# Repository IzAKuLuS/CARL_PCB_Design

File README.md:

This branch contains the PCB project for the battery management system project.

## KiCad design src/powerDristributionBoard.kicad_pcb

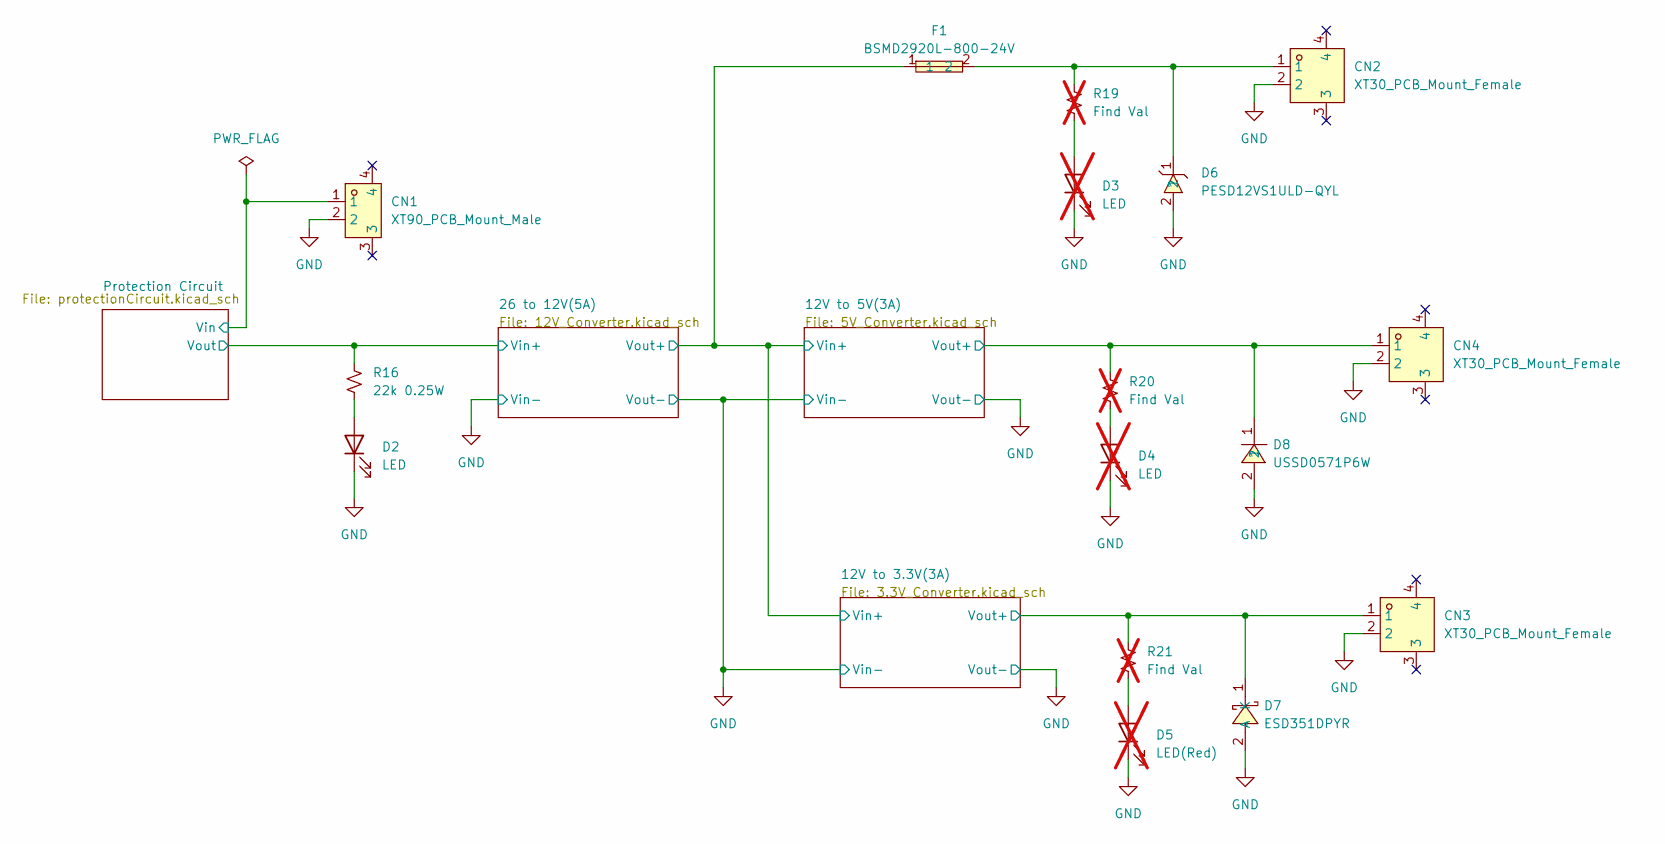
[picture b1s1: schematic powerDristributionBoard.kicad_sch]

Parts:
CN1: XT90_PCB_Mount_Male; XT-90_PCB_Mount_Male; MPN XT90PW-M.G.Y; LCSC Part C3040689
CN2, CN3, CN4: XT30_PCB_Mount_Female; MPN XT30PW-F20.G.Y; LCSC Part C2913282
D2: LED; LED_1206_3216Metric; MPN E7YYD; LCSC Part C55382848
D3, D4: LED; LED_0603_1608Metric; not fitted
D5: LED(Red); LED_0603_1608Metric; not fitted
D6: PESD12VS1ULD-QYL; MPN PESD12VS1ULD-QYL; LCSC Part C7508737
D7: ESD351DPYR; MPN ESD351DPYR; LCSC Part C1974929
D8: USSD0571P6W; MPN USSD0571P6W; LCSC Part C5272748
F1: BSMD2920L-800-24V; MPN BSMD2920L-800-24V; LCSC Part C51025748
R16: 22k 0.25W; R_1206_3216Metric; MPN HRC1206J223 HNTN; LCSC Part C54921593
R19, R20, R21: Find Val; R_0603_1608Metric; not fitted

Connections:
/12V to 3.3V(3A)/Vout+: CN3.1, D7.1 (K), R21.1; also elsewhere on the board
/12V to 5V(3A)/Vout+: CN4.1, D8.1, R20.1; also elsewhere on the board
/26 to 12V(5A)/Rsense+: F1.1; also elsewhere on the board
/Protection Circuit/Vin: CN1.1; also elsewhere on the board
GND: CN1.2, CN2.2, CN3.2, CN4.2, D2.1 (K), D3.1 (K), D4.1 (K), D5.1 (K), D6.2, D7.2 (A), D8.2; also elsewhere on the board
LM_Vin: R16.1; also elsewhere on the board
unnamed: CN2.1, D6.1, F1.2, R19.1
unnamed: D2.2 (A), R16.2
unnamed: D3.2 (A), R19.2
unnamed: D4.2 (A), R20.2
unnamed: D5.2 (A), R21.2

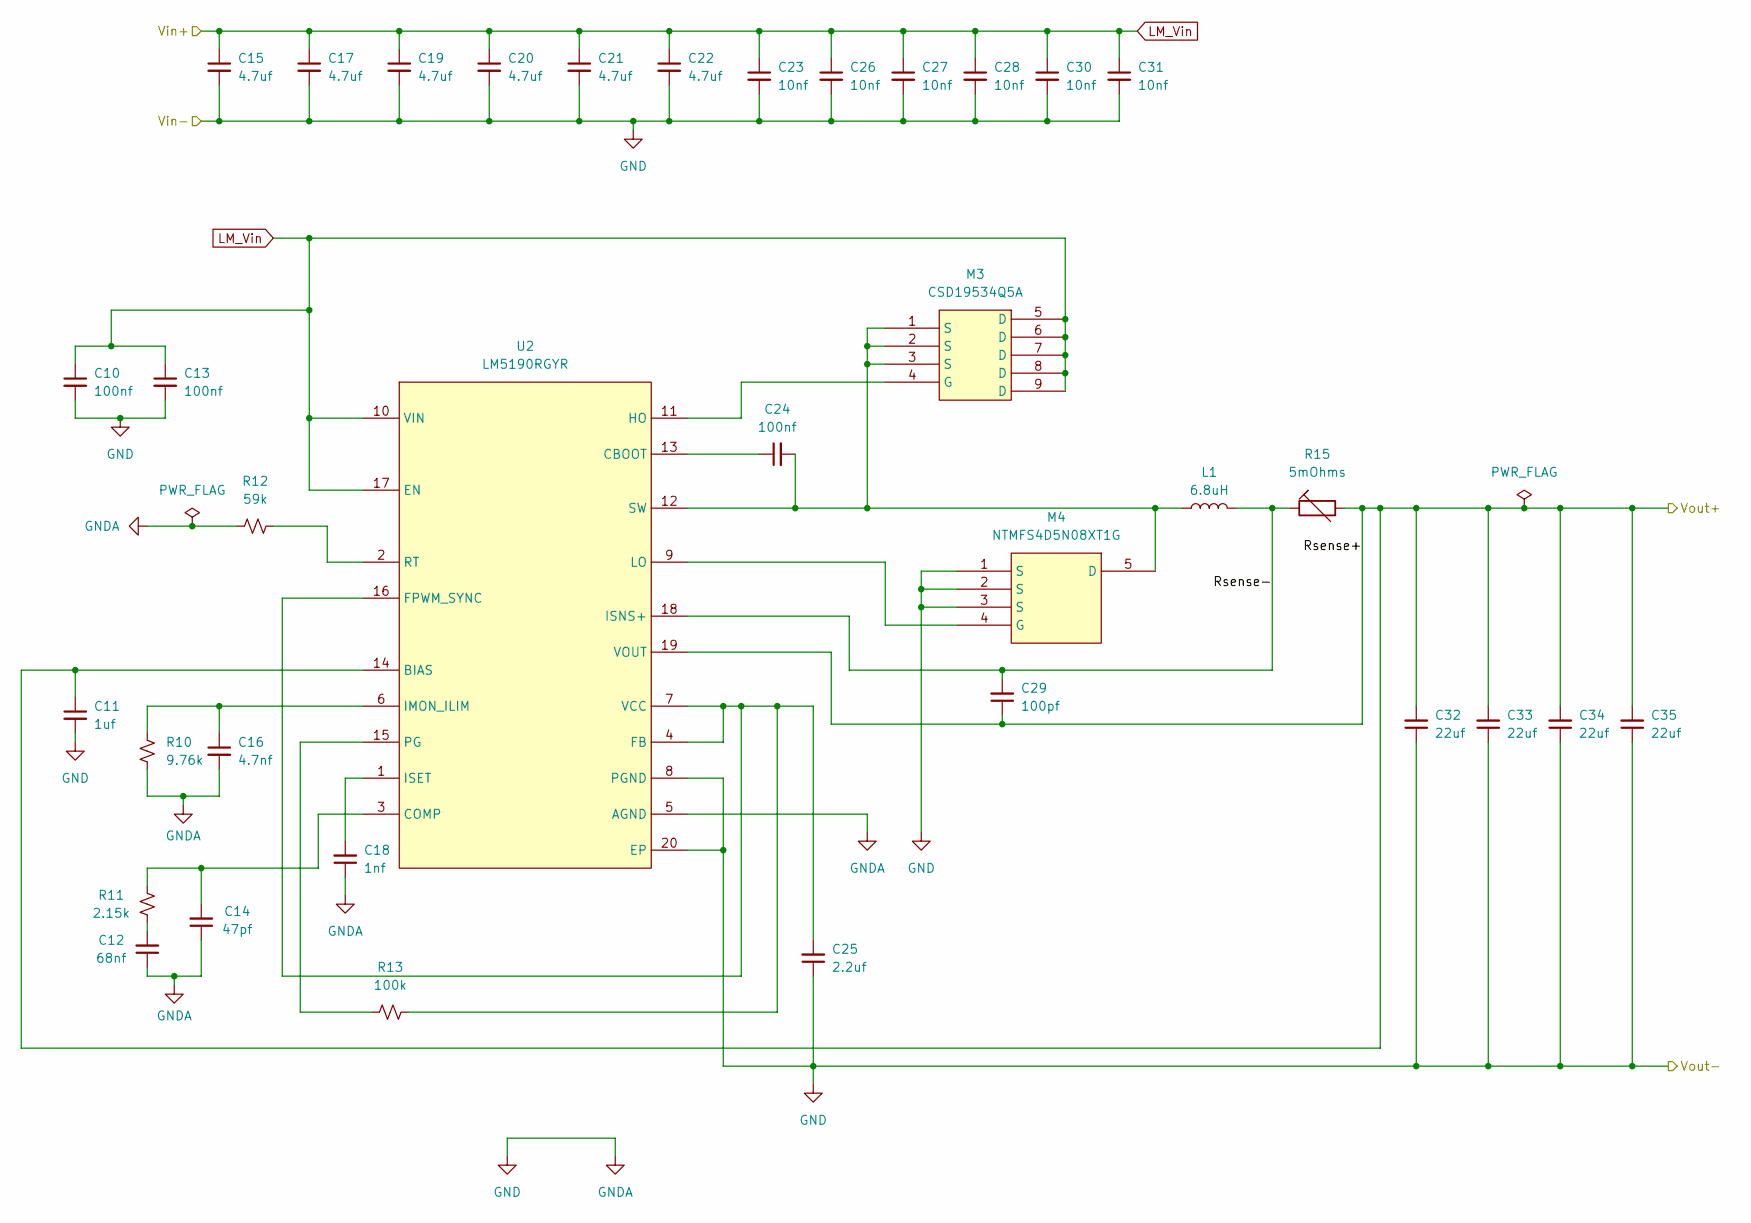
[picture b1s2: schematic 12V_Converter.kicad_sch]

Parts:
C10, C13, C24: 100nf; C_0603_1608Metric; MPN CC0603KRX7R7BB104; LCSC Part C108079
C11: 1uf; C_0603_1608Metric; MPN EMK107B7105KA-T; LCSC Part C92759
C12: 68nf; C_0603_1608Metric; MPN CC0603JRX7R9BB683; LCSC Part C309475
C14: 47pf; C_0603_1608Metric; MPN 06035A470JAT2A; LCSC Part C513324
C15, C17, C19, C20, C21, C22: 4.7uf; C_1210_3225Metric; MPN FS32X475K101EGG; LCSC Part C381466
C16: 4.7nf; C_0603_1608Metric; MPN C1608C0G1E472JT000N; LCSC Part C445739
C18: 1nf; C_0402_1005Metric; MPN GRM155R61A102KA01D; LCSC Part C710873
C23, C26, C27, C28, C30, C31: 10nf; C_0603_1608Metric; MPN AC0603JRX7R0BB103; LCSC Part C1853238
C25: 2.2uf; C_0603_1608Metric; MPN GRM188R71A225KE15D; LCSC Part C86018
C29: 100pf; C_0603_1608Metric; MPN 0603CG101J250NT; LCSC Part C336627
C32, C33, C34, C35: 22uf; C_1210_3225Metric; MPN CS3225X7R226K250NRL; LCSC Part C2918511
L1: 6.8uH; SMTC1010A-6R8MT; MPN SMTC1010A-6R8MT; LCSC Part C5445338
M3: CSD19534Q5A; MANUFACTURER_PART_NUMBER CSD19534Q5A; LCSC Part C2876530
M4: NTMFS4D5N08XT1G; MPN NTMFS4D5N08XT1G; LCSC Part C50727203
R10: 9.76k; R_0805_2012Metric; MPN ERJ6ENF9761V; LCSC Part C2077551
R11: 2.15k; R_0805_2012Metric; MPN 0805W8F2151T5E; LCSC Part C17516
R12: 59k; R_0603_1608Metric; MPN 0603WAF5902T5E; LCSC Part C23085
R13: 100k; R_0603_1608Metric; MPN CRCW0603100KFKEA; LCSC Part C844916
R15: 5mOhms; CSNL2010; MPN CSNL2010FT5L00; LCSC Part C6490398
U2: LM5190RGYR; MPN LM5190RGYR; LCSC Part C43351172

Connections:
/26 to 12V(5A)/Rsense+: C11.1, C29.1, C32.2, C33.2, C34.2, C35.2, R15.2, U2.14 (BIAS), U2.19 (VOUT); also elsewhere on the board
/26 to 12V(5A)/Rsense-: C29.2, L1.2, R15.1, U2.18 (ISNS+)
GND: C10.2, C11.2, C12.1, C13.2, C14.1, C15.2, C16.2, C17.2, C18.1, C19.2, C20.2, C21.2, C22.2, C23.2, C25.1, C26.2, C27.2, C28.2, C30.2, C31.2, C32.1, C33.1, C34.1, C35.1, M4.1 (S), M4.2 (S), M4.3 (S), R10.1, R12.1, U2.5 (AGND), U2.8 (PGND), U2.20 (EP); also elsewhere on the board
LM_Vin: C10.1, C13.1, C15.1, C17.1, C19.1, C20.1, C21.1, C22.1, C23.1, C26.1, C27.1, C28.1, C30.1, C31.1, M3.5 (D), M3.6 (D), M3.7 (D), M3.8 (D), M3.9 (D), U2.10 (VIN), U2.17 (EN); also elsewhere on the board
unnamed: C12.2, R11.2
unnamed: M3.4 (G), U2.11 (HO)
unnamed: C24.2, L1.1, M3.1 (S), M3.2 (S), M3.3 (S), M4.5 (D), U2.12 (SW)
unnamed: M4.4 (G), U2.9 (LO)
unnamed: C24.1, U2.13 (CBOOT)
unnamed: C14.2, R11.1, U2.3 (COMP)
unnamed: C25.2, R13.1, U2.4 (FB), U2.7 (VCC), U2.16 (FPWM_SYNC)
unnamed: C16.1, R10.2, U2.6 (IMON_ILIM)
unnamed: C18.2, U2.1 (ISET)
unnamed: R13.2, U2.15 (PG)
unnamed: R12.2, U2.2 (RT)

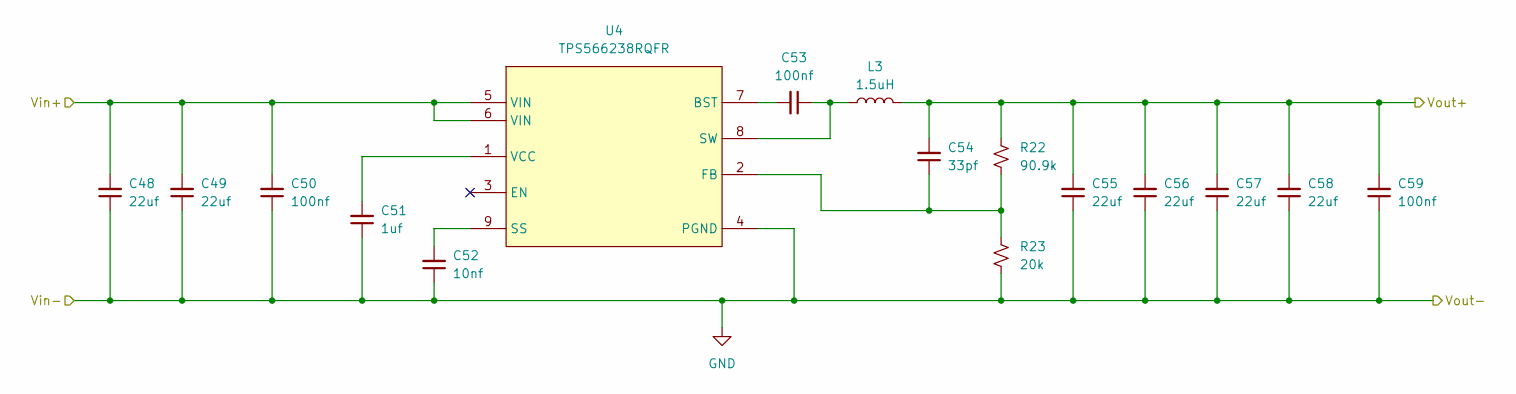
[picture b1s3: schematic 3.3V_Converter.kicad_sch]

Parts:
C48, C49, C55, C56, C57, C58: 22uf; C_0805_2012Metric; MPN MSAST21GBB5226MTNC12; LCSC Part C5677683
C50, C59: 100nf; C_0603_1608Metric; MPN CC0603KRX7R7BB104; LCSC Part C108079
C51: 1uf; C_0603_1608Metric; MPN C0603C105Z8VACTU; LCSC Part C2180996
C52: 10nf; C_0402_1005Metric; MPN GRM155R71C103KA01D; LCSC Part C85735
C53: 100nf; C_0402_1005Metric; MPN GRM155R71C104KA88D; LCSC Part C71629
C54: 33pf; C_0402_1005Metric; MPN CC0402JRNPO9BN330; LCSC Part C107005
L3: 1.5uH; SPM6530T-1R5M100; MPN SPM6530T-1R5M100; LCSC Part C76854
R22: 90.9k; R_0805_2012Metric; MPN ERJ6ENF9092V; LCSC Part C2078245
R23: 20k; R_0805_2012Metric; MPN CRCW080520K0FKEA; LCSC Part C844940
U4: TPS566238RQFR; MPN TPS566238RQFR; LCSC Part C5219353

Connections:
/12V to 3.3V(3A)/Vout+: C54.2, C55.2, C56.2, C57.2, C58.2, C59.2, L3.2, R22.1; also elsewhere on the board
/26 to 12V(5A)/Rsense+: C48.2, C49.2, C50.2, U4.5 (VIN), U4.6 (VIN); also elsewhere on the board
GND: C48.1, C49.1, C50.1, C51.1, C52.1, C55.1, C56.1, C57.1, C58.1, C59.1, R23.2, U4.4 (PGND); also elsewhere on the board
unnamed: C53.2, U4.7 (BST)
unnamed: C54.1, R22.2, R23.1, U4.2 (FB)
unnamed: C52.2, U4.9 (SS)
unnamed: C53.1, L3.1, U4.8 (SW)
unnamed: C51.2, U4.1 (VCC)

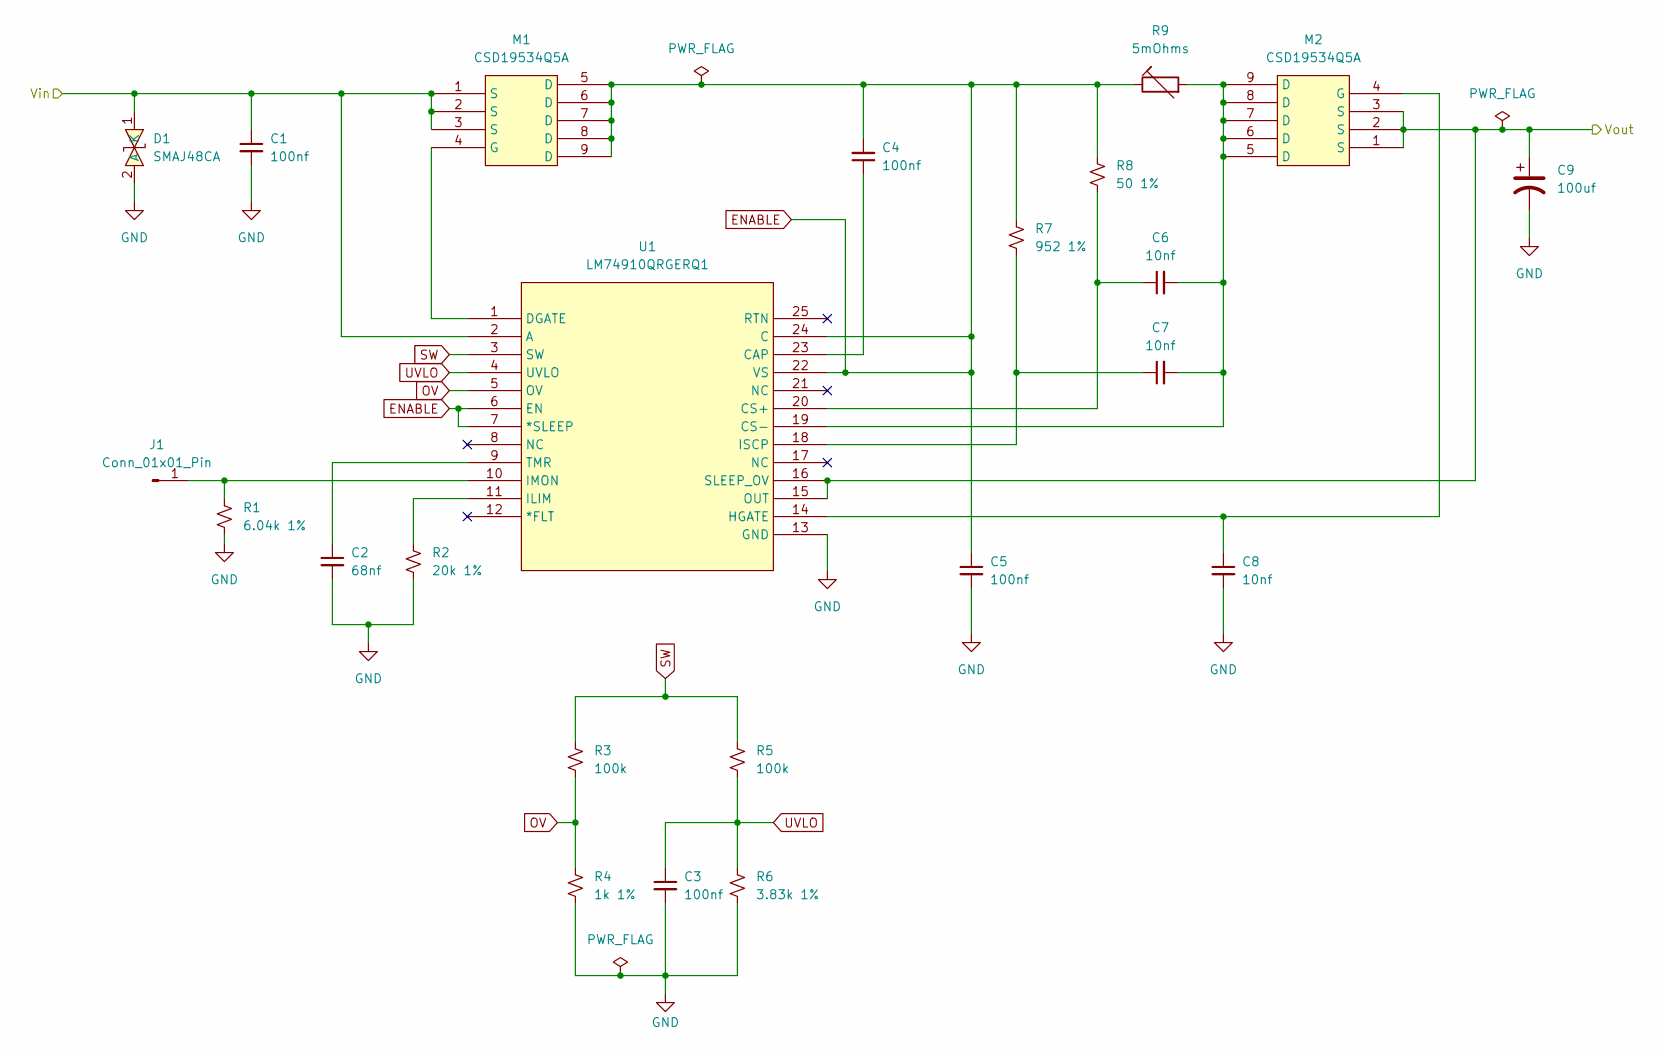
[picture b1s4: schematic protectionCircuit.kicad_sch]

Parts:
C1: 100nf; C_1210_3225Metric; MPN CC1210KKX7R0BB104; LCSC Part C527375
C2: 68nf; C_0603_1608Metric; MPN CC0603JRX7R9BB683; LCSC Part C309475
C3, C4, C5: 100nf; C_0603_1608Metric; MPN CC0603KRX7R7BB104; LCSC Part C108079
C6, C7, C8: 10nf; C_0603_1608Metric; MPN AC0603JRX7R0BB103; LCSC Part C1853238
C9: 100uf; 100uf_100V_SMD; MPN EFVH100ADA101M10C0; LCSC Part C22387799
D1: SMAJ48CA; MPN SMAJ48CA; LCSC Part C151245
J1: Conn_01x01_Pin; Single_THT_Pin
M1, M2: CSD19534Q5A; MANUFACTURER_PART_NUMBER CSD19534Q5A; LCSC Part C2876530
R1: 6.04k 1%; R_0603_1608Metric; MPN 0603WAF6041T5E; LCSC Part C25977
R2: 20k 1%; R_0603_1608Metric; MPN ERJ3EKF2002V; LCSC Part C403057
R3, R5: 100k; R_0603_1608Metric; MPN CRCW0603100KFKEA; LCSC Part C844916
R4: 1k 1%; R_0603_1608Metric; MPN ESR03EZPF1001; LCSC Part C2653986
R6: 3.83k 1%; R_0603_1608Metric; MPN GR0603F3K83T5G00; LCSC Part C49654961
R7: 952 1%; R_0603_1608Metric; MPN WR06X9530FTL; LCSC Part C334839
R8: 50 1%; R_0603_1608Metric; MPN CRCW060350R0FKEA; LCSC Part C844932
R9: 5mOhms; CSNL2010; MPN CSNL2010FT5L00; LCSC Part C6490398
U1: LM74910QRGERQ1; MANUFACTURER_PART_NUMBER LM74910QRGERQ1; LCSC Part C22427891

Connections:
/Protection Circuit/Vin: C1.1, D1.1 (K), M1.1 (S), M1.2 (S), M1.3 (S), U1.2 (A); also elsewhere on the board
ENABLE: C4.2, C5.1, M1.5 (D), M1.6 (D), M1.7 (D), M1.8 (D), M1.9 (D), R7.1, R8.1, R9.1, U1.6 (EN), U1.7 (*SLEEP), U1.22 (VS), U1.24 (C)
GND: C1.2, C2.2, C3.2, C5.2, C8.2, C9.2, D1.2 (A), R1.2, R2.2, R4.2, R6.2, U1.13 (GND); also elsewhere on the board
LM_Vin: C9.1, M2.1 (S), M2.2 (S), M2.3 (S), U1.15 (OUT), U1.16 (SLEEP_OV); also elsewhere on the board
unnamed 14: J1.1, R1.1, U1.10 (IMON); also elsewhere on the board
unnamed: M1.4 (G), U1.1 (DGATE)
unnamed: C8.1, M2.4 (G), U1.14 (HGATE)
unnamed: C4.1, U1.23 (CAP)
unnamed: C6.1, R8.2, U1.20 (CS+)
unnamed: C6.2, C7.2, M2.5 (D), M2.6 (D), M2.7 (D), M2.8 (D), M2.9 (D), R9.2, U1.19 (CS-)
unnamed: R2.1, U1.11 (ILIM)
unnamed: C7.1, R7.2, U1.18 (ISCP)
unnamed: C2.1, U1.9 (TMR)
OV: R3.2, R4.1, U1.5 (OV)
SW: R3.1, R5.1, U1.3 (SW)
UVLO: C3.1, R5.2, R6.1, U1.4 (UVLO)

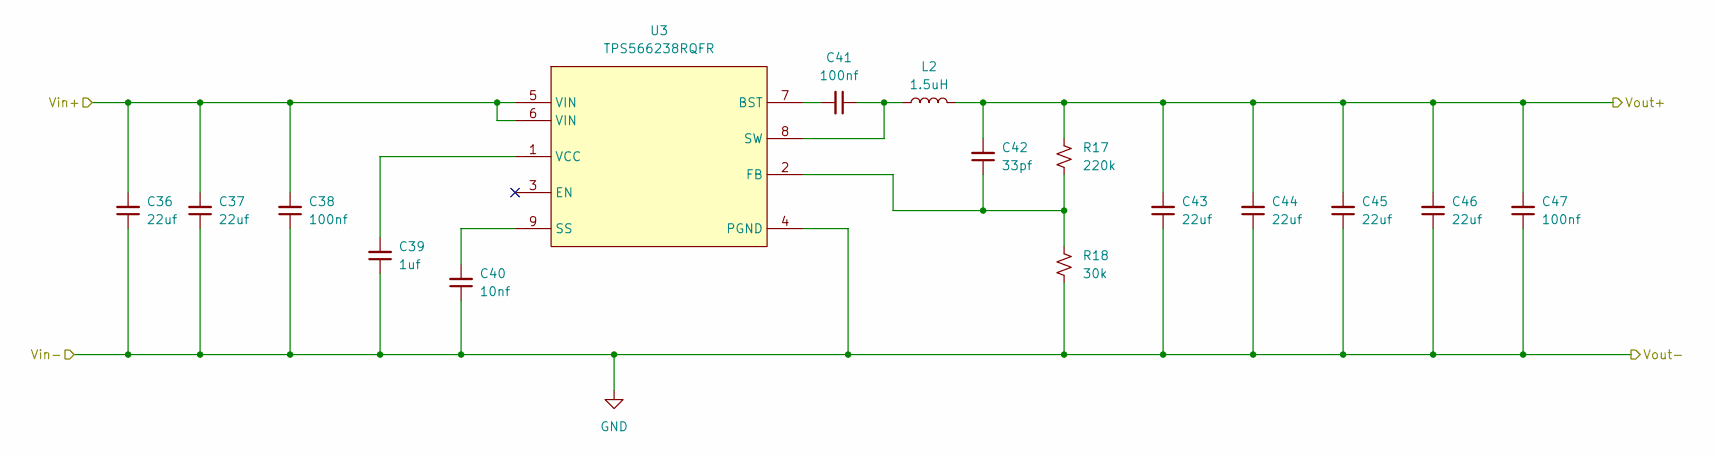
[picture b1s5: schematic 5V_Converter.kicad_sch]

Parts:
C36, C37, C43, C44, C45, C46: 22uf; C_0805_2012Metric; MPN MSAST21GBB5226MTNC12; LCSC Part C5677683
C38, C47: 100nf; C_0603_1608Metric; MPN CC0603KRX7R7BB104; LCSC Part C108079
C39: 1uf; C_0603_1608Metric; MPN C0603C105Z8VACTU; LCSC Part C2180996
C40: 10nf; C_0402_1005Metric; MPN GRM155R71C103KA01D; LCSC Part C85735
C41: 100nf; C_0402_1005Metric; MPN GRM155R71C104KA88D; LCSC Part C71629
C42: 33pf; C_0402_1005Metric; MPN CC0402JRNPO9BN330; LCSC Part C107005
L2: 1.5uH; SPM6530T-1R5M100; MPN SPM6530T-1R5M100; LCSC Part C76854
R17: 220k; R_0603_1608Metric; MPN RC0603FR-07220KL; LCSC Part C123420
R18: 30k; R_0603_1608Metric; MPN RC0603FR-0730KL; LCSC Part C100001
U3: TPS566238RQFR; MPN TPS566238RQFR; LCSC Part C5219353

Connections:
/12V to 5V(3A)/Vout+: C42.2, C43.2, C44.2, C45.2, C46.2, C47.2, L2.2, R17.2; also elsewhere on the board
/26 to 12V(5A)/Rsense+: C36.2, C37.2, C38.2, U3.5 (VIN), U3.6 (VIN); also elsewhere on the board
GND: C36.1, C37.1, C38.1, C39.1, C40.1, C43.1, C44.1, C45.1, C46.1, C47.1, R18.1, U3.4 (PGND); also elsewhere on the board
unnamed: C41.2, U3.7 (BST)
unnamed: C42.1, R17.1, R18.2, U3.2 (FB)
unnamed: C40.2, U3.9 (SS)
unnamed: C41.1, L2.1, U3.8 (SW)
unnamed: C39.2, U3.1 (VCC)

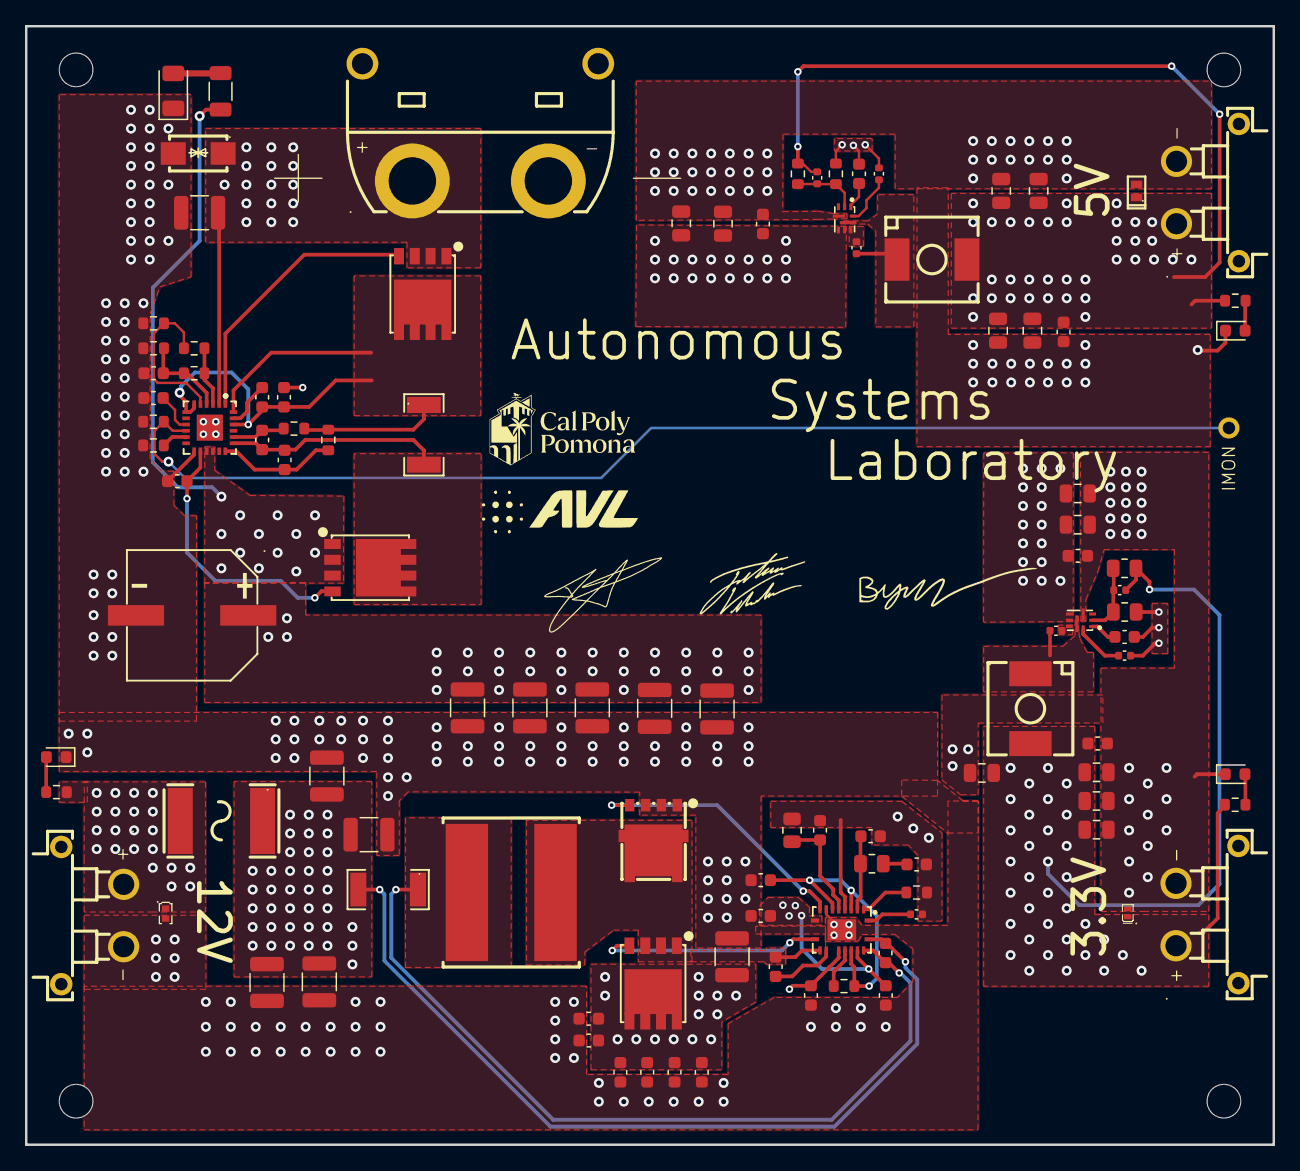
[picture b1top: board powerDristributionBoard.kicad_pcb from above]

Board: 4 copper layers, 100.0 x 89.7 mm, 106 parts (0 on the bottom side), 46 nets.

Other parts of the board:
3.3V, 5V: XT30_PCB_Mount_Female
IMON: Conn_01x01_Pin; Single_THT_Pin

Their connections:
/12V to 3.3V(3A)/Vout+: 3.3V.1; also elsewhere on the board
/12V to 5V(3A)/Vout+: 5V.1; also elsewhere on the board
GND: 3.3V.2, 5V.2; also elsewhere on the board
unnamed 14: IMON.1 (Pin_1_1); also elsewhere on the board

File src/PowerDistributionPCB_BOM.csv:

"Reference","Qty","Value","DNP","Exclude from BOM","Footprint","LCSC Part","MPN","Manufacturer"
"C1","1","100nf","","","Capacitor_SMD:C_1210_3225Metric","C527375","CC1210KKX7R0BB104","YAGEO"
"C2,C12","2","68nf","","","Capacitor_SMD:C_0603_1608Metric","C309475","CC0603JRX7R9BB683","YAGEO"
"C3,C4,C5,C10,C13,C24,C38,C47,C50,C59","10","100nf","","","Capacitor_SMD:C_0603_1608Metric","C108079","CC0603KRX7R7BB104","YAGEO"
"C6,C7,C8,C23,C26,C27,C28,C30,C31","9","10nf","","","Capacitor_SMD:C_0603_1608Metric","C1853238","AC0603JRX7R0BB103","YAGEO"
"C9","1","100uf","","","PowerPCB_Footprints:100uf_100V_SMD","C22387799","EFVH100ADA101M10C0","FOLLON"
"C11,C39,C51","3","1uf","","","Capacitor_SMD:C_0603_1608Metric","C2180996,C92759","C0603C105Z8VACTU,EMK107B7105KA-T","KEMET,Taiyo Yuden"
"C14","1","47pf","","","Capacitor_SMD:C_0603_1608Metric","C513324","06035A470JAT2A","--"
"C15,C17,C19,C20,C21,C22","6","4.7uf","","","Capacitor_SMD:C_1210_3225Metric","C381466","FS32X475K101EGG","PSA(Prosperity Dielectrics)"
"C16","1","4.7nf","","","Capacitor_SMD:C_0603_1608Metric","C445739","C1608C0G1E472JT000N","TDK"
"C18","1","1nf","","","Capacitor_SMD:C_0402_1005Metric","C710873","GRM155R61A102KA01D","Murata Electronics"
"C25","1","2.2uf","","","Capacitor_SMD:C_0603_1608Metric","C86018","GRM188R71A225KE15D","Murata Electronics"
"C29","1","100pf","","","Capacitor_SMD:C_0603_1608Metric","C336627","0603CG101J250NT","FH (Guangdong Fenghua Advanced Tech)"
"C32,C33,C34,C35","4","22uf","","","Capacitor_SMD:C_1210_3225Metric","C2918511","CS3225X7R226K250NRL","Samwha Capacitor"
"C36,C37,C43,C44,C45,C46,C48,C49,C55,C56,C57,C58","12","22uf","","","Capacitor_SMD:C_0805_2012Metric","C5677683","MSAST21GBB5226MTNC12","Taiyo Yuden"
"C40,C52","2","10nf","","","Capacitor_SMD:C_0402_1005Metric","C85735","GRM155R71C103KA01D","Murata Electronics"
"C41,C53","2","100nf","","","Capacitor_SMD:C_0402_1005Metric","C71629","GRM155R71C104KA88D","Murata Electronics"
"C42,C54","2","33pf","","","Capacitor_SMD:C_0402_1005Metric","C107005","CC0402JRNPO9BN330","YAGEO"
"CN1","1","XT90_PCB_Mount_Male","","","PowerPCB_Footprints:XT-90_PCB_Mount_Male","C3040689","XT90PW-M.G.Y","AMASS(艾迈斯)"
"CN2,CN3,CN4","3","XT30_PCB_Mount_Female","","","PowerPCB_Footprints:XT30_PCB_Mount_Female","C2913282","XT30PW-F20.G.Y","AMASS(艾迈斯)"
"D1","1","SMAJ48CA","","","PowerPCB_Footprints:SMAJ48CA","C151245","SMAJ48CA","Littelfuse(美国力特)"
"D2","1","LED","","","LED_SMD:LED_1206_3216Metric","C55382848","E7YYD","Beking Optoelectronics"
"D6","1","PESD12VS1ULD-QYL","","","PowerPCB_Footprints:PESD12VS1ULD-QYL","C7508737","PESD12VS1ULD-QYL","Nexperia(安世)"
"D7","1","ESD351DPYR","","","PowerPCB_Footprints:ESD351DPYR","C1974929","ESD351DPYR","TI(德州仪器)"
"D8","1","USSD0571P6W","","","PowerPCB_Footprints:USSD0571P6W","C5272748","USSD0571P6W","Leiditech(雷卯电子)"
"F1","1","BSMD2920L-800-24V","","","PowerPCB_Footprints:BSMD2920L-800-24V","C51025748","BSMD2920L-800-24V","BHFUSE(佰宏)"
"L1","1","6.8uH","","","PowerPCB_Footprints:SMTC1010A-6R8MT","C5445338","SMTC1010A-6R8MT","SXN(Shun Xiang Nuo Elec)"
"L2,L3","2","1.5uH","","","PowerPCB_Footprints:SPM6530T-1R5M100","C76854","SPM6530T-1R5M100","TDK"
"M1,M2,M3","3","CSD19534Q5A","","","PowerPCB_Footprints:CSD19534Q5A","C2876530","CSD19534Q5AT","Texas Instruments"
"M4","1","NTMFS4D5N08XT1G","","","PowerPCB_Footprints:NTMFS4D5N08XT1G","C50727203","NTMFS4D5N08XT1G","onsemi"
"R1","1","6.04k 1%","","","Resistor_SMD:R_0603_1608Metric","C25977","0603WAF6041T5E","UNI-ROYAL(Uniroyal Elec)"
"R2","1","20k 1%","","","Resistor_SMD:R_0603_1608Metric","C403057","ERJ3EKF2002V","PANASONIC"
"R3,R5,R13","3","100k","","","Resistor_SMD:R_0603_1608Metric","C844916","CRCW0603100KFKEA","Vishay Intertech"
"R4","1","1k 1%","","","Resistor_SMD:R_0603_1608Metric","C2653986","ESR03EZPF1001","ROHM Semicon"
"R6","1","3.83k 1%","","","Resistor_SMD:R_0603_1608Metric","C49654961","GR0603F3K83T5G00","GiantOhm"
"R7","1","952 1%","","","Resistor_SMD:R_0603_1608Metric","C334839","WR06X9530FTL","Walsin Tech Corp"
"R8","1","50 1%","","","Resistor_SMD:R_0603_1608Metric","C844932","CRCW060350R0FKEA","Vishay Intertech"
"R9,R15","2","5mOhms","","","PowerPCB_Footprints:CSNL2010","C6490398","CSNL2010FT5L00","SEI(Stackpole Elec)"
"R10","1","9.76k","","","Resistor_SMD:R_0805_2012Metric","C2077551","ERJ6ENF9761V","PANASONIC"
"R11","1","2.15k","","","Resistor_SMD:R_0805_2012Metric","C17516","0805W8F2151T5E","UNI-ROYAL(Uniroyal Elec)"
"R12","1","59k","","","Resistor_SMD:R_0603_1608Metric","C23085","0603WAF5902T5E","UNI-ROYAL(Uniroyal Elec)"
"R16","1","22k 0.25W","","","Resistor_SMD:R_1206_3216Metric","C54921593","HRC1206J223 HNTN","HWA CHN"
"R17","1","220k","","","Resistor_SMD:R_0603_1608Metric","C123420","RC0603FR-07220KL","YAGEO"
"R18","1","30k","","","Resistor_SMD:R_0603_1608Metric","C100001","RC0603FR-0730KL","YAGEO"
"R22","1","90.9k","","","Resistor_SMD:R_0805_2012Metric","C2078245","ERJ6ENF9092V","PANASONIC"
"R23","1","20k","","","Resistor_SMD:R_0805_2012Metric","C844940","CRCW080520K0FKEA","Vishay Intertech"
"U1","1","LM74910QRGERQ1","","","PowerPCB_Footprints:LM74910QRGERQ1","C22427891","LM74910QRGERQ1","Texas Instruments"
"U2","1","LM5190RGYR","","","PowerPCB_Footprints:LM5190RGYR","C43351172","LM5190RGYR","Texas Instruments"
"U3,U4","2","TPS566238RQFR","","","PowerPCB_Footprints:TPS566238RQFR","C5219353","TPS566238RQFR","Texas Instruments"

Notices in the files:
parts and their libraries:
Copyright: Copyright (C) 2026 Ultra Librarian. All rights reserved.
Copyright: Copyright (C) 2025 Ultra Librarian. All rights reserved.
